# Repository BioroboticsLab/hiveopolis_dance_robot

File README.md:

# Hiveopolis Dance Robot

This will list the documents and files for constructing the bee robot.

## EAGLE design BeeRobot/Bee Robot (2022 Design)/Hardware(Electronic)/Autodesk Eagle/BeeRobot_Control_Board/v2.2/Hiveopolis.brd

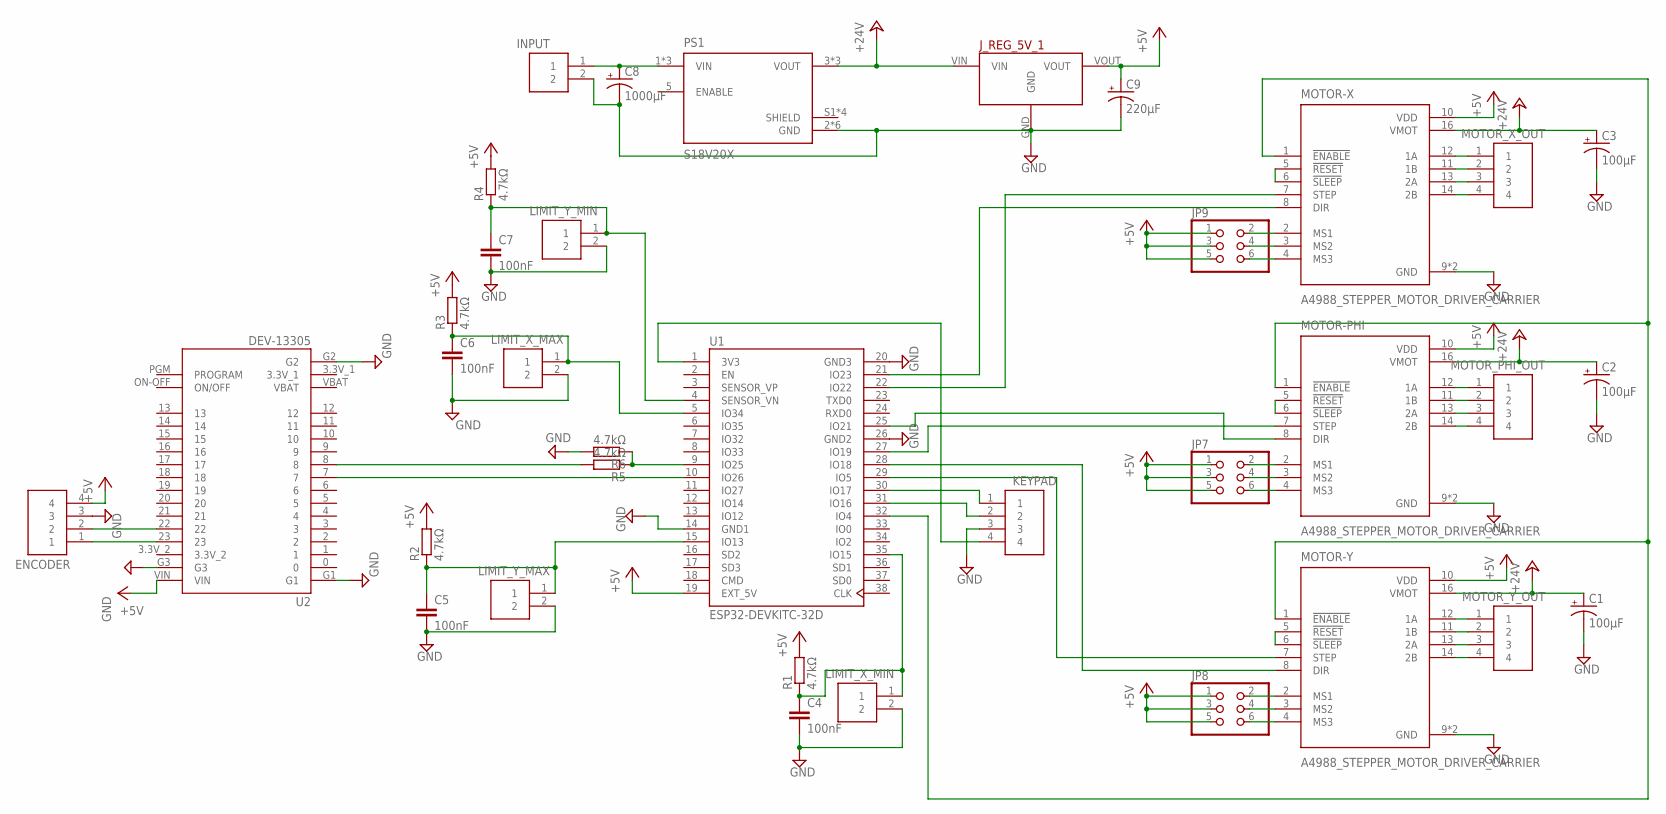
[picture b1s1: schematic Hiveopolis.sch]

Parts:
C1, C2, C3: 100µF; E5-5
C4, C5, C6, C7: 100nF; C025-024X044
C8: 1000µF; E5-10,5
C9: 220µF; E5-8,5
ENCODER: S4B-XH-A(LF)(SN); HDR-04/RA
INPUT: S2B-XH-A(LF)(SN); HDR-02/RA
JP7, JP8, JP9: PINHD-2X3; 2X03
J_REG_5V_1: 5V_VOLTAGE_REGULATOR
KEYPAD: S4B-XH-A(LF)(SN); HDR-04/RA
LIMIT_X_MAX: S2B-XH-A(LF)(SN); HDR-02/RA
LIMIT_X_MIN: S2B-XH-A(LF)(SN); HDR-02/RA
LIMIT_Y_MAX: S2B-XH-A(LF)(SN); HDR-02/RA
LIMIT_Y_MIN: S2B-XH-A(LF)(SN); HDR-02/RA
MOTOR-PHI: A4988_STEPPER_MOTOR_DRIVER_CARRIER; MODULE_A4988_STEPPER_MOTOR_DRIVER_CARRIER
MOTOR-X: A4988_STEPPER_MOTOR_DRIVER_CARRIER; MODULE_A4988_STEPPER_MOTOR_DRIVER_CARRIER
MOTOR-Y: A4988_STEPPER_MOTOR_DRIVER_CARRIER; MODULE_A4988_STEPPER_MOTOR_DRIVER_CARRIER
MOTOR_PHI_OUT: S4B-XH-A(LF)(SN); HDR-04/RA
MOTOR_X_OUT: S4B-XH-A(LF)(SN); HDR-04/RA
MOTOR_Y_OUT: S4B-XH-A(LF)(SN); HDR-04/RA
PS1: S18V20X; CONV_S18V20X
R1, R2, R3, R4, R5, R6: 4.7kΩ; 0207/10
U1: ESP32-DEVKITC-32D; MODULE_ESP32-DEVKITC-32D
U2: DEV-13305; MODULE_DEV-13305

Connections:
3.3V_1: U2.3.3V_1
3.3V_2: U2.3.3V_2
+5V: C9.+, ENCODER.4, JP7.1, JP7.3, JP7.5, JP8.1, JP8.3, JP8.5, JP9.1, JP9.3, JP9.5, J_REG_5V_1.VOUT, MOTOR-PHI.10 (VDD), MOTOR-X.10 (VDD), MOTOR-Y.10 (VDD), R1.2, R2.2, R3.2, R4.2, U1.19 (EXT_5V), U2.VIN
+24V: C1.+, C2.+, C3.+, J_REG_5V_1.VIN, MOTOR-PHI.16 (VMOT), MOTOR-X.16 (VMOT), MOTOR-Y.16 (VMOT), PS1.3 (VOUT), PS1.10 (VOUT), PS1.11 (VOUT)
GND: C1.-, C2.-, C3.-, C4.2, C5.2, C6.2, C7.2, C8.-, C9.-, ENCODER.3, INPUT.2, J_REG_5V_1.GND, KEYPAD.3, LIMIT_X_MAX.2, LIMIT_X_MIN.2, LIMIT_Y_MAX.2, LIMIT_Y_MIN.2, MOTOR-PHI.9 (GND), MOTOR-PHI.15 (GND), MOTOR-X.9 (GND), MOTOR-X.15 (GND), MOTOR-Y.9 (GND), MOTOR-Y.15 (GND), PS1.2 (GND), PS1.4 (GND), PS1.8 (GND), PS1.9 (GND), PS1.12 (GND), PS1.13 (GND), R6.2, U1.14 (GND1), U1.20 (GND3), U1.26 (GND2), U2.G1, U2.G2, U2.G3
unnamed: MOTOR-X.7 (STEP), U1.22 (IO22)
unnamed: MOTOR-X.8 (DIR), U1.21 (IO23)
unnamed: R5.2, U2.8
unnamed: JP9.2, MOTOR-X.2 (MS1)
unnamed: MOTOR-PHI.8 (DIR), U1.25 (IO21)
unnamed: MOTOR-Y.7 (STEP), U1.29 (IO5)
unnamed: C5.1, LIMIT_Y_MAX.1, R2.1, U1.15 (IO13)
unnamed: MOTOR-PHI.7 (STEP), U1.27 (IO19)
unnamed: MOTOR-X.12 (1A), MOTOR_X_OUT.1
unnamed: MOTOR-X.11 (1B), MOTOR_X_OUT.2
unnamed: MOTOR-X.13 (2A), MOTOR_X_OUT.3
unnamed: MOTOR-X.14 (2B), MOTOR_X_OUT.4
unnamed: JP9.4, MOTOR-X.3 (MS2)
unnamed: JP9.6, MOTOR-X.4 (MS3)
unnamed: JP7.2, MOTOR-PHI.2 (MS1)
unnamed: JP7.4, MOTOR-PHI.3 (MS2)
unnamed: MOTOR-PHI.12 (1A), MOTOR_PHI_OUT.1
unnamed: MOTOR-PHI.11 (1B), MOTOR_PHI_OUT.2
unnamed: MOTOR-PHI.13 (2A), MOTOR_PHI_OUT.3
unnamed: MOTOR-PHI.14 (2B), MOTOR_PHI_OUT.4
unnamed: MOTOR-Y.12 (1A), MOTOR_Y_OUT.1
unnamed: MOTOR-Y.11 (1B), MOTOR_Y_OUT.2
unnamed: MOTOR-Y.13 (2A), MOTOR_Y_OUT.3
unnamed: MOTOR-Y.14 (2B), MOTOR_Y_OUT.4
unnamed: JP7.6, MOTOR-PHI.4 (MS3)
unnamed: JP8.2, MOTOR-Y.2 (MS1)
unnamed: C6.1, LIMIT_X_MAX.1, R3.1, U1.5 (IO34)
unnamed: U1.10 (IO26), U2.7
unnamed: KEYPAD.1, U1.30 (IO17)
unnamed: C7.1, LIMIT_Y_MIN.1, R4.1, U1.4 (SENSOR_VN)
unnamed: JP8.4, MOTOR-Y.3 (MS2)
unnamed: JP8.6, MOTOR-Y.4 (MS3)
unnamed: KEYPAD.2, U1.31 (IO16)
unnamed: KEYPAD.4, U1.1 (3V3)
unnamed: C4.1, LIMIT_X_MIN.1, R1.1, U1.35 (IO15)
unnamed: MOTOR-PHI.5 (!RESET), MOTOR-PHI.6 (!SLEEP)
unnamed: MOTOR-PHI.1 (!ENABLE), MOTOR-X.1 (!ENABLE), MOTOR-Y.1 (!ENABLE), U1.32 (IO4)
unnamed: R5.1, R6.1, U1.9 (IO25)
unnamed: C8.+, INPUT.1, PS1.1 (VIN), PS1.6 (VIN), PS1.7 (VIN)
unnamed: MOTOR-Y.5 (!RESET), MOTOR-Y.6 (!SLEEP)
unnamed: MOTOR-Y.8 (DIR), U1.28 (IO18)
unnamed: MOTOR-X.5 (!RESET), MOTOR-X.6 (!SLEEP)
unnamed: ENCODER.1, U2.23
unnamed: ENCODER.2, U2.22
VBAT: U2.VBAT

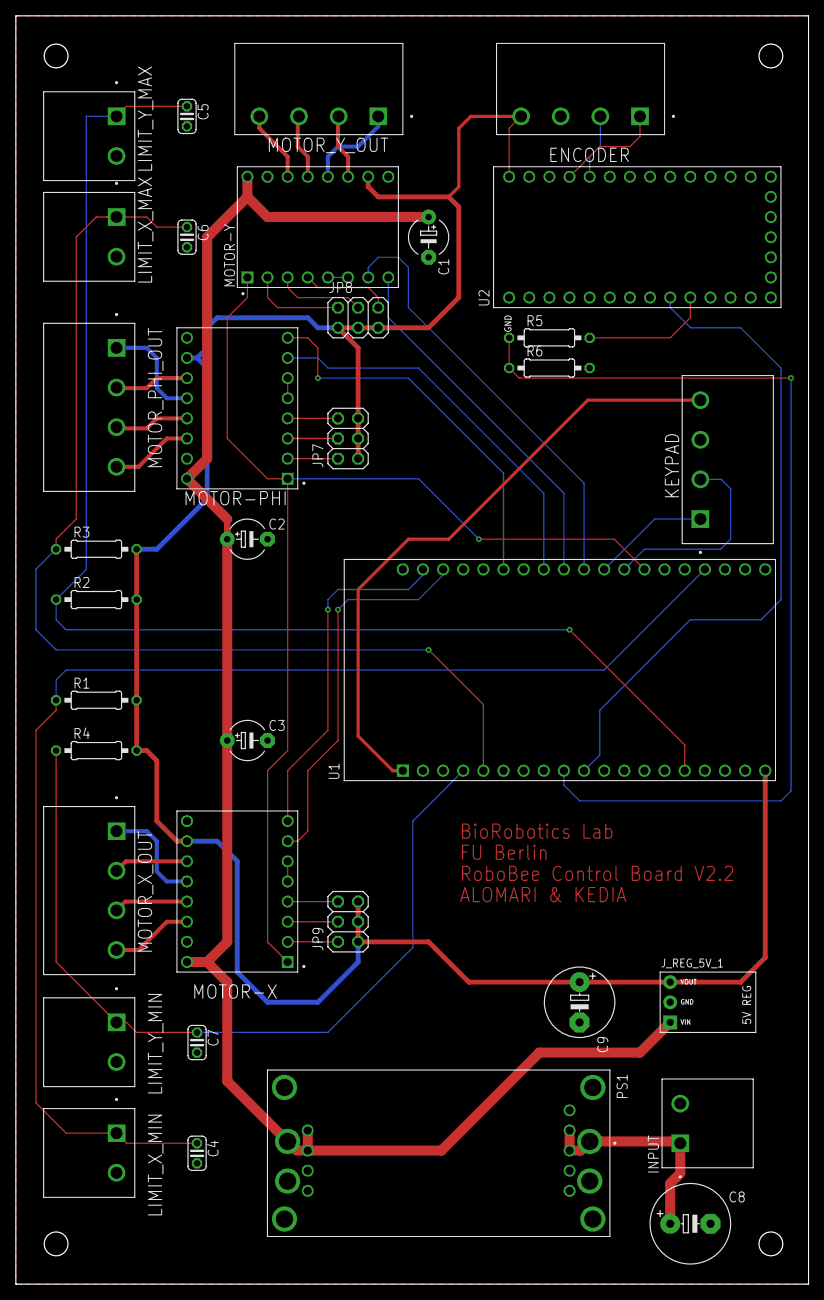
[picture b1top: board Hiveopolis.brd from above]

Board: 2 copper layers, 99.8 x 159.8 mm, 35 parts (0 on the bottom side), 47 nets.

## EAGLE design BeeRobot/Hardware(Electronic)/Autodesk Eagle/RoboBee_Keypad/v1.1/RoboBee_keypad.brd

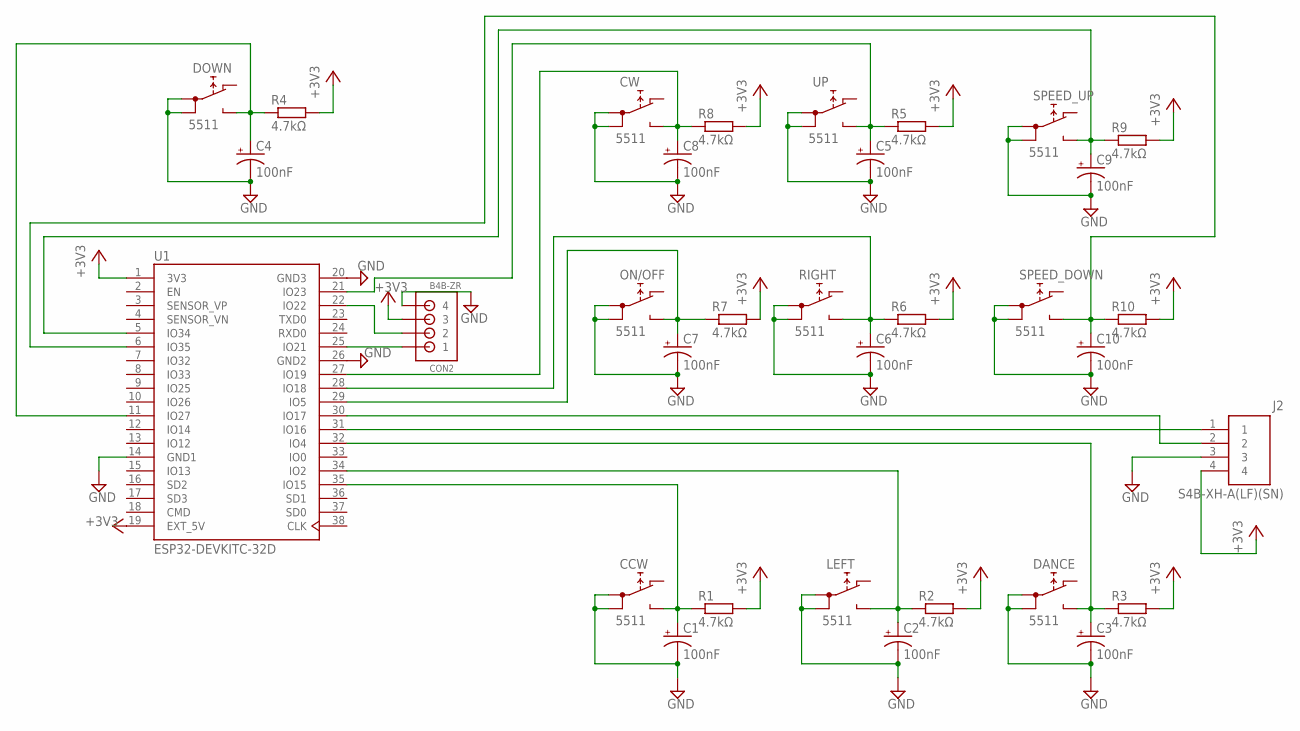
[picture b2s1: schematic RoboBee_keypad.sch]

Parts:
C1, C2, C3, C4, C5, C6, C7, C8, C9, C10: 100nF; E1,8-4
CCW: 5511
CON2: B4B-ZR
CW: 5511
DANCE: 5511
DOWN: 5511
J2: S4B-XH-A(LF)(SN); HDR-04/RA
LEFT: 5511
ON/OFF: 5511
R1, R2, R3, R4, R5, R6, R7, R8, R9, R10: 4.7kΩ; 0207/10
RIGHT: 5511
SPEED_DOWN: 5511
SPEED_UP: 5511
U1: ESP32-DEVKITC-32D; MODULE_ESP32-DEVKITC-32D
UP: 5511

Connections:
+3V3: CON2.3, J2.4, R1.2, R2.2, R3.2, R4.2, R5.2, R6.2, R7.2, R8.2, R9.2, R10.2, U1.1 (3V3), U1.19 (EXT_5V)
GND: C1.-, C2.-, C3.-, C4.-, C5.-, C6.-, C7.-, C8.-, C9.-, C10.-, CCW.1A, CCW.1B, CON2.4, CW.1A, CW.1B, DANCE.1A, DANCE.1B, DOWN.1A, DOWN.1B, J2.3, LEFT.1A, LEFT.1B, ON/OFF.1A, ON/OFF.1B, RIGHT.1A, RIGHT.1B, SPEED_DOWN.1A, SPEED_DOWN.1B, SPEED_UP.1A, SPEED_UP.1B, U1.14 (GND1), U1.20 (GND3), U1.26 (GND2), UP.1A, UP.1B
unnamed: C1.+, CCW.NO, R1.1, U1.35 (IO15)
unnamed: C2.+, LEFT.NO, R2.1, U1.34 (IO2)
unnamed: C3.+, DANCE.NO, R3.1, U1.32 (IO4)
unnamed: C4.+, DOWN.NO, R4.1, U1.11 (IO27)
unnamed: C5.+, R5.1, U1.21 (IO23), UP.NO
unnamed: C6.+, R6.1, RIGHT.NO, U1.28 (IO18)
unnamed: C8.+, CW.NO, R8.1, U1.27 (IO19)
unnamed: C7.+, ON/OFF.NO, R7.1, U1.29 (IO5)
unnamed: C10.+, R10.1, SPEED_DOWN.NO, U1.6 (IO35)
unnamed: CON2.1, U1.25 (IO21)
unnamed: J2.1, U1.31 (IO16)
unnamed: J2.2, U1.30 (IO17)
unnamed: CON2.2, U1.22 (IO22)
unnamed: C9.+, R9.1, SPEED_UP.NO, U1.5 (IO34)

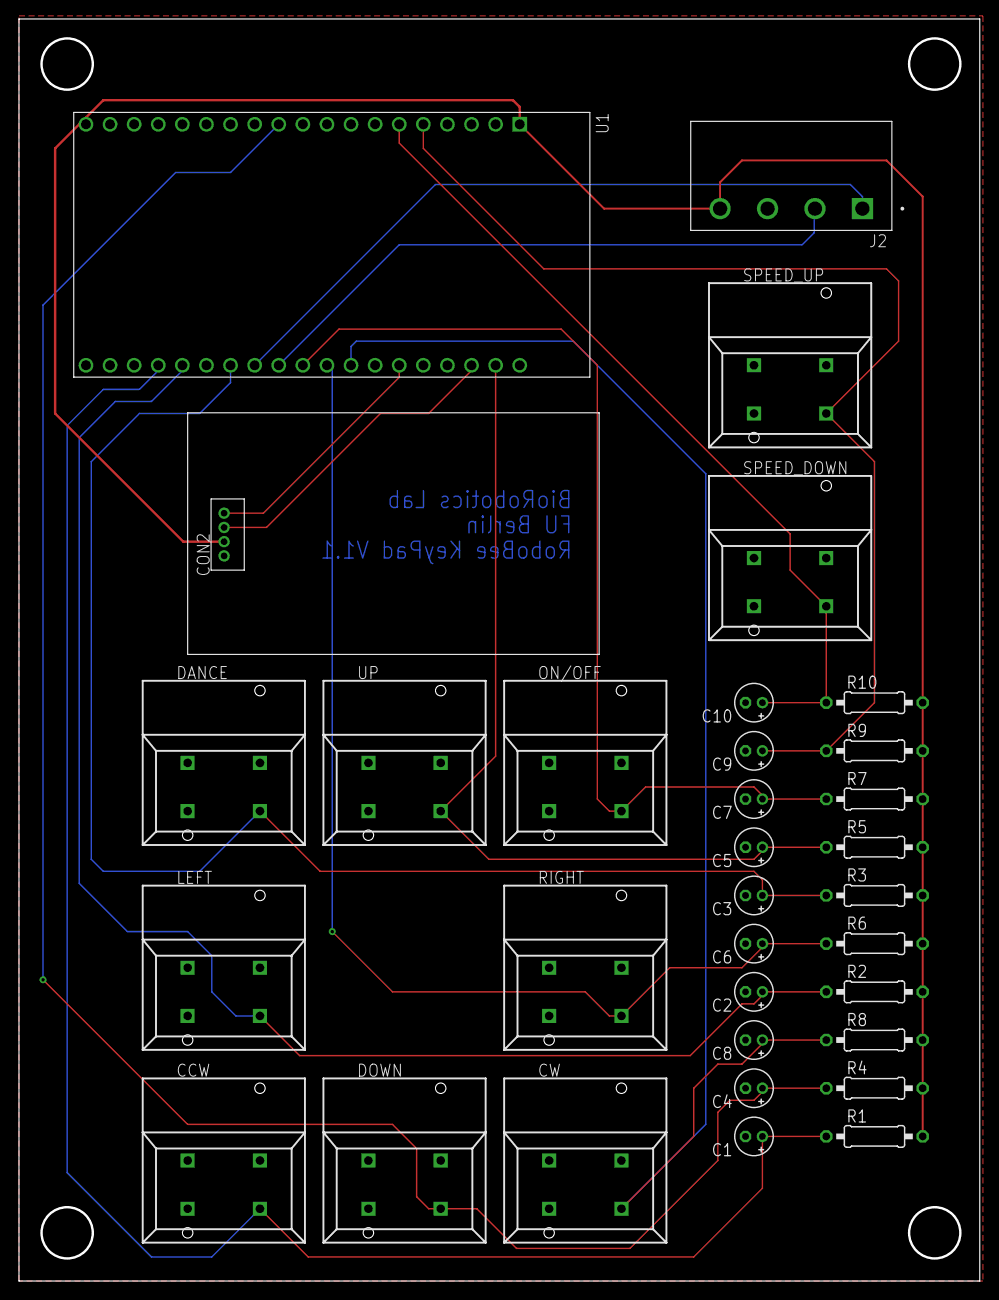
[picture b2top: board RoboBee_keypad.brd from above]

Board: 2 copper layers, 101.0 x 132.8 mm, 33 parts (0 on the bottom side), 16 nets.

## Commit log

2023-08-09 Added STL hardware files for Lights and camera fixture and mounts.
2023-08-09 Adding 3D Models of the ITEM Robot Fixture
2023-08-09 Added Encoder Code
2023-08-09 Added Matlab code for the trajectory model
2023-08-09 Bee Robot Electronic Hardware files added
2023-08-09 Added code files for the Keypad
2023-08-09 Folder reorganization
    Folder reorganization to create two versions of the Bee Robot i.e. 2022 version being the first one and the second one being the repurposed 3d plotter
2023-08-09 Added code for Main Board 2022 version
2023-08-09 Added code for MainBoard version 2023
    Code for MainBoard version for repurposed 3D Plotter
2023-08-09 Added CAD Files for the Bee Robot
    Added CAD Files for the Bee Robot for version 2022
